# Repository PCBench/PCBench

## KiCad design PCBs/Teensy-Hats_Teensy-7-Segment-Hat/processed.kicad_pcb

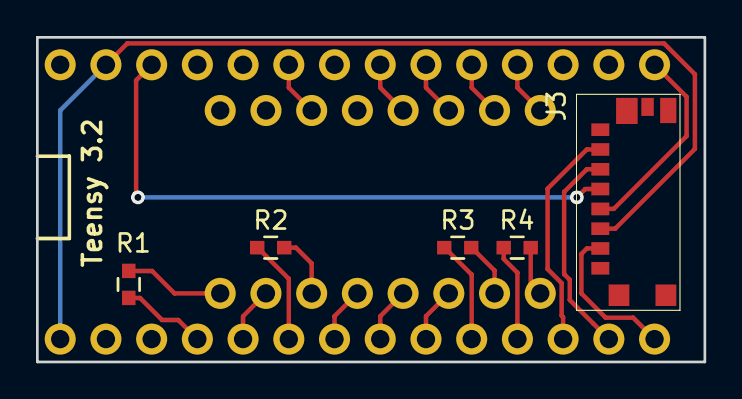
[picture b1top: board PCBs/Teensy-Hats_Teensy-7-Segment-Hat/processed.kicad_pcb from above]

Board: 2 copper layers, 37.1 x 18.0 mm, 7 parts (1 on the bottom side), 23 nets.

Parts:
J1: TEENSY3.2-72MHz-SIMPLE; TEENSY-3.2-SIMPLE
J3: MICRO-SD; CONN-SD-MICRO-MOLEX-0475710001
LED1: LED-4x7-SEGMENT-LTC-4727JR; DIP-16-W10.16MM-CIRCLEPADS
R1, R2, R3, R4: 470; RLC-0603-SMD

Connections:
+3V3: J1.3V2, J3.4
/A: J1.18, LED1.14
/B: J1.16, LED1.16
/C: J1.19, LED1.13
/D: J1.7, LED1.3
/DIGIT1: J1.9, R4.1
/DIGIT2: J1.8, R3.1
/DIGIT3: J1.4, R2.1
/DIGIT4: J1.2, R1.1
/DP: J1.3, LED1.7
/E: J1.5, LED1.5
/F: J1.21, LED1.11
/G: J1.17, LED1.15
/L: J1.6, LED1.4
/MISO: J1.12, J3.7
/MOSI: J1.11, J3.3
/SCLK: J1.13, J3.5
/SD_CS: J1.10, J3.2
GND: J1.AG, J1.G1, J3.6
unnamed: LED1.1, R4.2
unnamed: LED1.2, R3.2
unnamed: LED1.6, R2.2
unnamed: LED1.8, R1.2

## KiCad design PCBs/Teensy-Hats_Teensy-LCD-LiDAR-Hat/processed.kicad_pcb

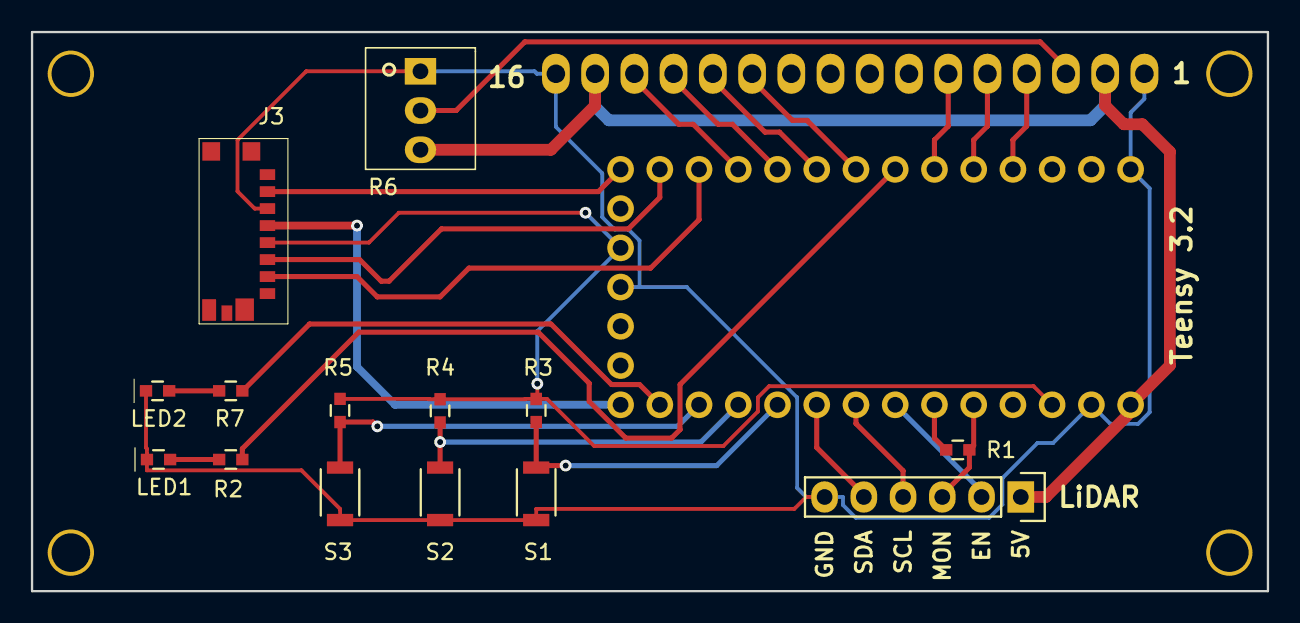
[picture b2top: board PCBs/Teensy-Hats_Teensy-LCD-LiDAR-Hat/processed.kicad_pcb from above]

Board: 2 copper layers, 80.0 x 36.2 mm, 16 parts (1 on the bottom side), 27 nets.

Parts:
J1: TEENSY3.2-72MHz; TEENSY-3.2-NOSILK
J2: LIDAR-LITE; CONN-HEADER-STRAIGHT-P2.54MM-1x06
J3: MICRO-SD; CONN-SD-MICRO-MOLEX-0475710001
LCD1: LCD-16x2; LCD-1602A
LED1, LED2: AMBER; LED-0603-SMD
R1, R2, R3, R4, R5, R7: 1K; RLC-0603-SMD
R6: 10K; RES-TRIMPOT-BOURNS-3362-SQUARE-TH-CENTER
S1: BUTTON1; SWITCH-OMRON-MOMENTARY-SMD-B3U-1000P
S2: BUTTON2; SWITCH-OMRON-MOMENTARY-SMD-B3U-1000P
S3: BUTTON3; SWITCH-OMRON-MOMENTARY-SMD-B3U-1000P

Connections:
+3V3: J1.3V1, J1.3V2, J3.4, R3.1, R4.1, R5.1
+5V: J1.VIN, J2.1, LCD1.2, LCD1.15, R6.3
/BUTTON1: J1.17, R3.2, S1.1
/BUTTON2: J1.16, R4.2, S2.1
/BUTTON3: J1.15, R5.2, S3.1
/LCD_D4: J1.6, LCD1.11
/LCD_D5: J1.7, LCD1.12
/LCD_D6: J1.8, LCD1.13
/LCD_D7: J1.9, LCD1.14
/LCD_EN: J1.4, LCD1.6
/LCD_RS: J1.2, LCD1.4
/LCD_RW: J1.3, LCD1.5
/LED1: J1.5, R2.1
/LED2: J1.14, R7.1
/LIDAR_EN: J1.20, J2.2
/LIDAR_MONITOR: J1.22, J2.3, R1.2
/LIDAR_TRIGGER: J1.21, R1.1
/MISO: J1.12, J3.7
/MOSI: J1.11, J3.3
/SCL: J1.19, J2.4
/SCLK: J1.13, J3.5
/SDA: J1.18, J2.5
/SD_CS: J1.10, J3.2
GND: J1.AG, J1.G1, J1.G2, J2.6, J3.6, LCD1.1, LCD1.16, LED1.1, LED2.1, R6.1, S1.2, S2.2, S3.2
unnamed: LCD1.3, R6.2
unnamed: LED1.2, R2.2
unnamed: LED2.2, R7.2

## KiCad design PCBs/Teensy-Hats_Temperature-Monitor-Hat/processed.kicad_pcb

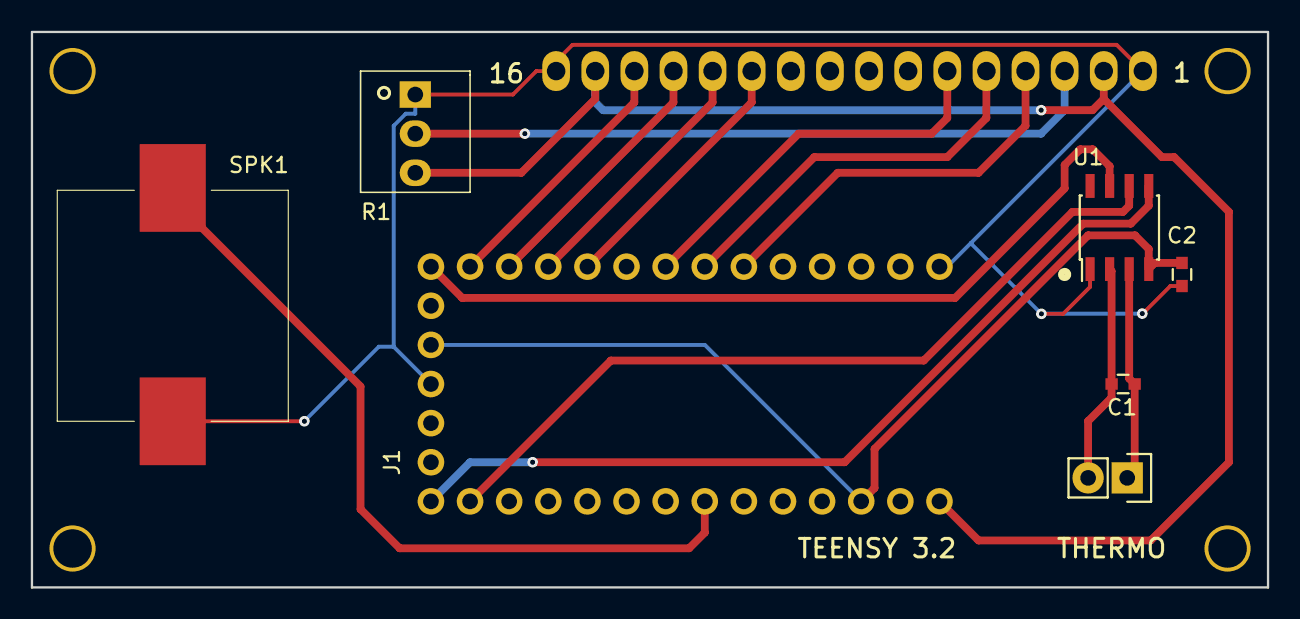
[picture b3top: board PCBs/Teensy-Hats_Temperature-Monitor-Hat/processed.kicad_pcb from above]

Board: 2 copper layers, 80.3 x 36.1 mm, 8 parts (1 on the bottom side), 17 nets.

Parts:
C1, C2: 100nF; RLC-0603-SMD
J1: TEENSY3.2-72MHz; TEENSY-3.2-NOSILK
J2: THERMO; CONN-ONSHORE-SCREW-GREEN-2PIN-TH
LCD1: LCD-MODULE-16X2-CHARACTER-1602A-CUSTOM1; LCD-1602A
R1: 10K; RES-TRIMPOT-BOURNS-3362-SQUARE-TH-CENTER
SPK1: BUZZER; SPEAKER-CMT-1603
U1: MAX31855; SOIC-8-3.9x4.9MM-P1.27MM

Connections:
+3V3: C2.1, J1.3V1, J1.3V2, U1.4
+5V: J1.VIN, LCD1.2, LCD1.15, R1.3
GND: C2.2, J1.G1, J1.G2, LCD1.1, LCD1.16, R1.1, SPK1.2, U1.1
unnamed: C1.1, J2.1, U1.3
unnamed: C1.2, J2.2, U1.2
unnamed: J1.4, LCD1.4
unnamed: J1.5, LCD1.5
unnamed: J1.6, LCD1.6
unnamed: J1.8, LCD1.11
unnamed: J1.9, LCD1.12
unnamed: J1.10, LCD1.13
unnamed: J1.11, LCD1.14
unnamed: J1.12, U1.7
unnamed: J1.13, U1.5
unnamed: J1.14, U1.6
unnamed: J1.20, SPK1.1
unnamed: LCD1.3, R1.2

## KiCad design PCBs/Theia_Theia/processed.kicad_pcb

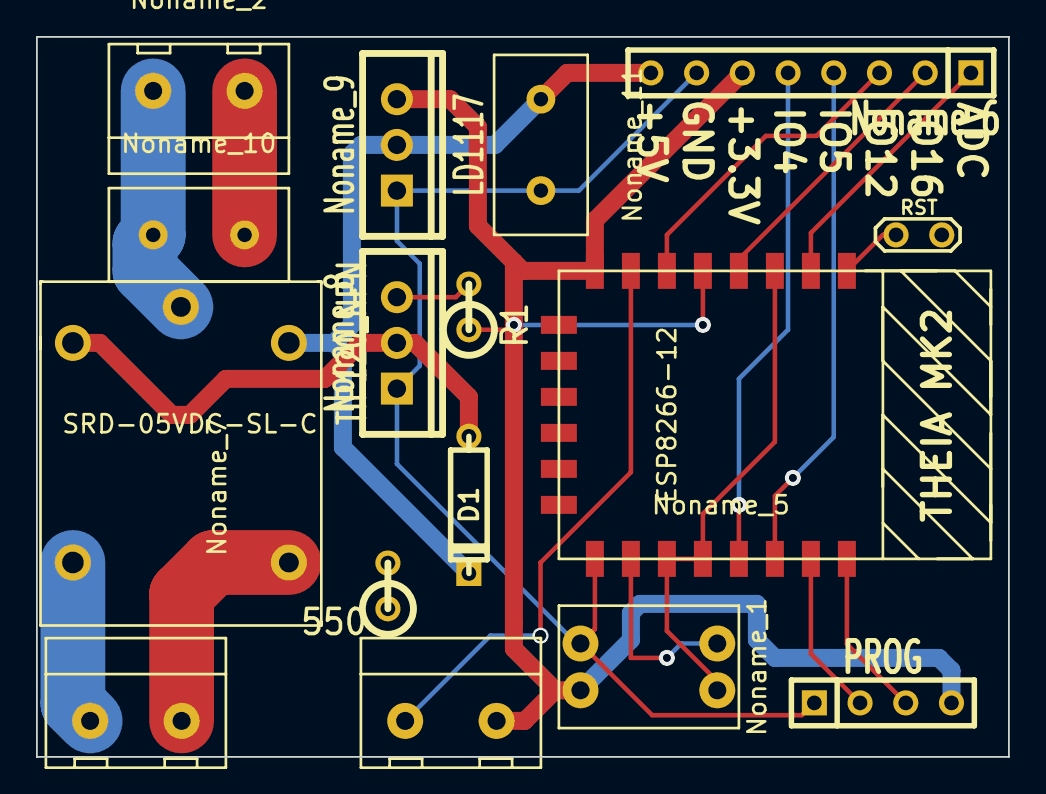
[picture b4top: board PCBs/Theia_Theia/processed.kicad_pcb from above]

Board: 2 copper layers, 54.0 x 40.0 mm, 16 parts (0 on the bottom side), 20 nets.

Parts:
550: R1
D1: 1N4001; D3
Noname_1: 2bit_dipsw
Noname_2, Noname_3, Noname_4: Conn2.54
Noname_5: ESP8266-12
Noname_6: SIL-8
Noname_7: SRD-05VDC-SL-C
Noname_8: TIP120_NPN; TO220_VERT
Noname_9: LD1117; TO220_VERT
Noname_10, Noname_11: Wire2.54
PROG: SIL-4
R1: 1kOhm; R1
RST: TESTPOINT

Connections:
+3.3V: Noname_1.3, Noname_4.1, Noname_5.8, Noname_6.6, Noname_9.2, PROG.4
+5V: D1.2, Noname_6.8, Noname_7.3, Noname_9.3, Noname_11.1
GNDA: Noname_1.1, Noname_5.15, Noname_6.7, Noname_8.1, Noname_9.1, Noname_11.2, PROG.1
LIVE: Noname_2.1, Noname_7.1, Noname_10.1
unnamed: Noname_5.19, Noname_6.5
unnamed: Noname_5.2, Noname_6.1
unnamed: Noname_3.1, Noname_7.5
unnamed: Noname_5.4, Noname_6.2
unnamed: Noname_5.6, Noname_6.3
unnamed: Noname_5.20, Noname_6.4
unnamed: Noname_3.2, Noname_7.4
unnamed: Noname_1.2, Noname_5.16
unnamed: Noname_5.5, R1.1
unnamed: Noname_8.2, R1.2
unnamed: Noname_4.2, Noname_5.7
unnamed: Noname_5.21, PROG.2
unnamed: Noname_5.22, PROG.3
unnamed: D1.1, Noname_7.2, Noname_8.3
unnamed: Noname_1.4, Noname_5.3, Noname_5.17, Noname_5.18
NEUT: Noname_2.2, Noname_10.2

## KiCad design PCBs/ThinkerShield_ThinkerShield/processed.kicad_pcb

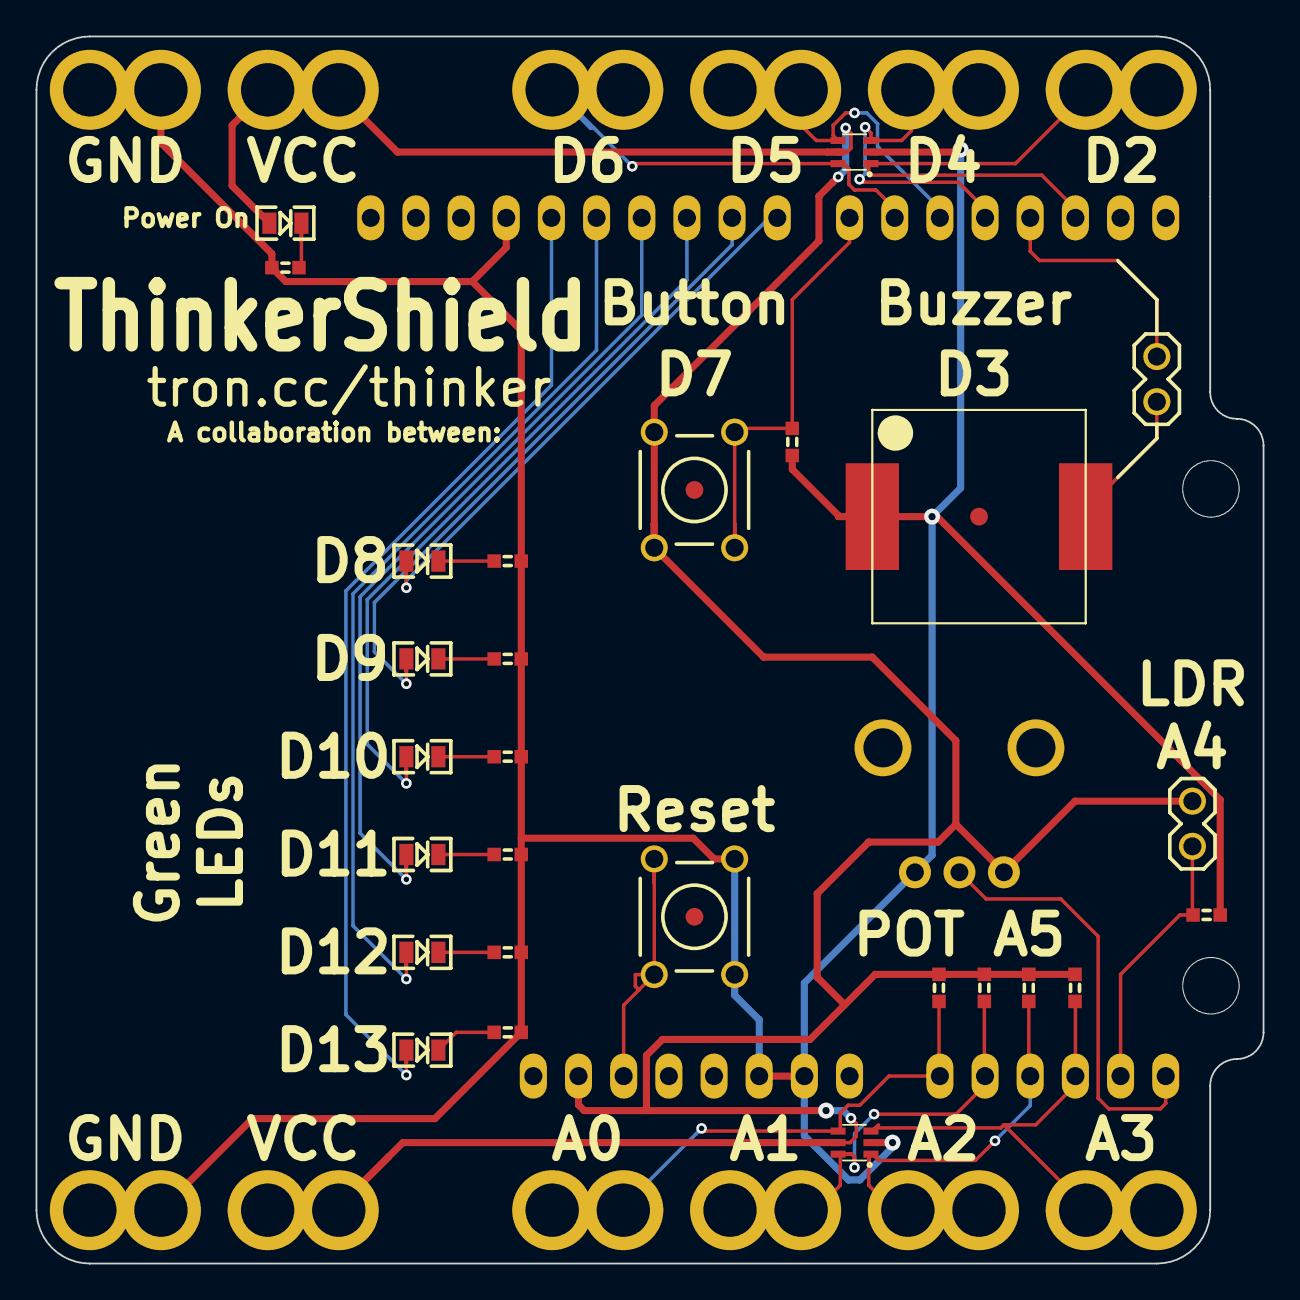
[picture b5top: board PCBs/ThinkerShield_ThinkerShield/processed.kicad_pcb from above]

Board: 2 copper layers, 69.0 x 69.0 mm, 46 parts (1 on the bottom side), 29 nets.

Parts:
FIDUCIAL: val**; FIDUCIAL
FIDUCIAL_2, FIDUCIAL_3: val**; FIDUCIAL
JP1, JP2, JP3, JP4, JP5, JP6, JP7, JP8, JP9, JP10, JP11, JP12: M01; ALLIGATOR_CLIP_CONN
JP13: JUMPER2; 1X02
LED1, LED2, LED3, LED4, LED5, LED6: GREEN; LED-0805
LED7: BLUE; LED-0805
LOGO_FREETRONICS: val**; LOGO_FREETRONICS_14mm_SolderMask
LOGO_FREETRONICS_2: val**; LOGO_FREETRONICS_33mm
PH1: LDR GL5516; 1X02
R1: 1K; 0603
R2: 10K; 0603
R3, R4, R10, R11, R12, R13: 470R; 0603
R5, R7, R8, R9: 22M; 0603
R6: 2.2K; 0603
SHIELD1: ARDUINO_SHIELD
SW1, SW2: SW_PUSHBUTTON; SW_PUSHBUTTON_PTH
TV1, TV2: SMF05C; SOT363
U1: BUZZER; BUZZER-12X12-SMT
VR1: 10K; POT_RV09_VERT

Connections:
/A0: JP1.1, R5.1, SHIELD1.AD0, TV1.4
/A1: JP2.1, R7.1, SHIELD1.AD1, TV1.6
/A2: JP3.1, R8.1, SHIELD1.AD2, TV1.1
/A3: JP4.1, R9.1, SHIELD1.AD3, TV1.3
/A4: PH1.2, R1.1, SHIELD1.AD4
/A5: SHIELD1.AD5, VR1.W
/BUZZER: JP13.2, U1.2
/D2: JP9.1, SHIELD1.2, TV2.1
/D3: JP13.1, SHIELD1.3
/D4: JP10.1, SHIELD1.4, TV2.3
/D5: JP11.1, SHIELD1.5, TV2.4
/D6: JP12.1, SHIELD1.6, TV2.6
/D7: R2.1, SHIELD1.7, SW2.2
/D8: LED1.A, SHIELD1.8
/D9: LED2.A, SHIELD1.9
/D10: LED3.A, SHIELD1.10
/D11: LED4.A, SHIELD1.11
/D12: LED5.A, SHIELD1.12
/D13: LED6.A, SHIELD1.13
GND: JP7.1, JP8.1, R1.2, R2.2, R3.1, R4.1, R6.1, R10.1, R11.1, R12.1, R13.1, SHIELD1.GND1, SHIELD1.GND2, SHIELD1.GND3, SW1.2, TV1.2, TV2.2, U1.1, VR1.1
IORef: JP5.1, JP6.1, LED7.A, PH1.1, R5.2, R7.2, R8.2, R9.2, SHIELD1.IO_R, SW2.1, TV1.5, TV2.5, VR1.2
unnamed: LED1.K, R3.2
unnamed: LED2.K, R4.2
unnamed: LED3.K, R10.2
unnamed: LED4.K, R11.2
unnamed: LED5.K, R12.2
unnamed: LED6.K, R13.2
unnamed: LED7.K, R6.2
unnamed: SHIELD1.RST, SW1.1

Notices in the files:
PCBs/Teensy-Hats_Temperature-Monitor-Hat/processed.kicad_pcb:
Released under the CERN Open Hardware License v1.2
PCBs/ThinkerShield_ThinkerShield/processed.kicad_pcb:
Copyright (C) 2015 Freetronics Pty Ltd
TAPR Open Hardware License: tapr.org/ohl
